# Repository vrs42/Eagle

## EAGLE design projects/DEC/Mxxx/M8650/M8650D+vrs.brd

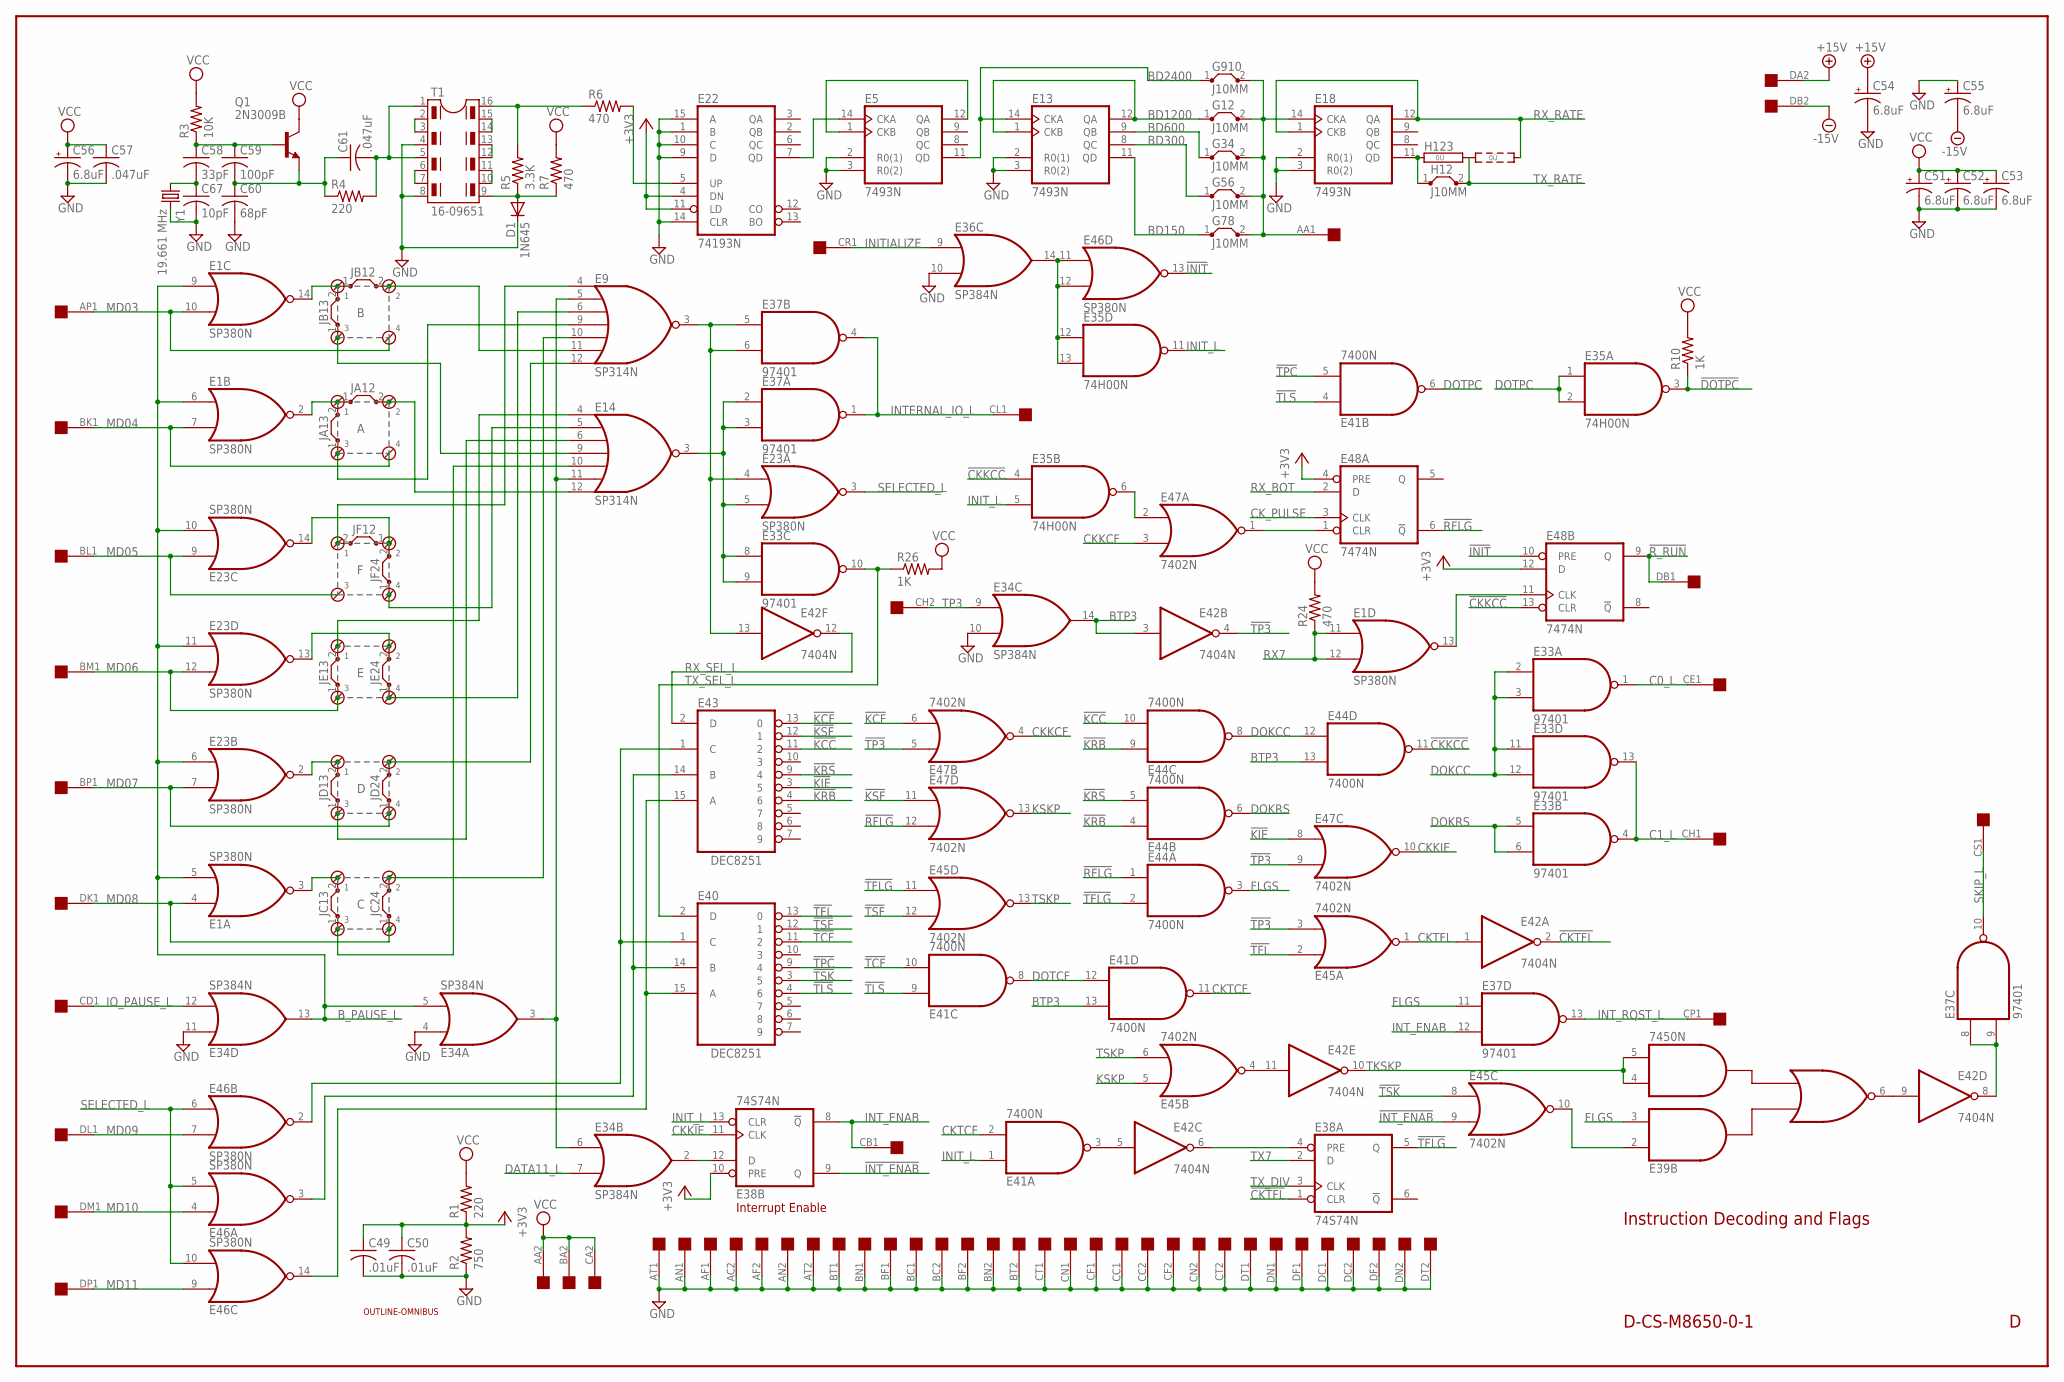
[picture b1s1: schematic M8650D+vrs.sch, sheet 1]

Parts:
A: JUMPER4
B: JUMPER4
C: JUMPER4
C49, C50: .01uF; C050-025X075
C51, C52, C53, C54, C55, C56: 6.8uF; E12-8
C57, C61: .047uF; C050-025X075
C58: 33pF; C050-025X075
C59: 100pF; C050-025X075
C60: 68pF; C050-025X075
C67: 10pF; C050-025X075
D: JUMPER4
D1: 1N645; DO35-10
E: JUMPER4
E1, E23, E46: SP380N; DIL14
E5, E13, E18: 7493N; DIL14
E9, E14: SP314N; DIL14
E22: 74193N; DIL16
E33, E37: 97401; DIL14
E34, E36: SP384N; DIL14
E35: 74H00N; DIL14
E38: 74S74N; DIL14
E39: 7450N; DIL14
E40, E43: DEC8251; DIL16
E41, E44: 7400N; DIL14
E42: 7404N; DIL14
E45, E47: 7402N; DIL14
E48: 7474N; DIL14
F: JUMPER4
G12, G34, G56, G78, G910: J10MM; 10
H12: J10MM; 10
H123: 0R2; 0R2/10
JA12, JA13: J10MM; 10
JB12, JB13: J10MM; 10
JC13, JC24: J10MM; 10
JD13, JD24: J10MM; 10
JE13, JE24: J10MM; 10
JF12, JF24: J10MM; 10
Q1: 2N3009B; TO5
R1, R4: 220; 0207/10
R2: 750; 0207/10
R3: 10K; 0207/10
R5: 3.3K; 0207/10
R6, R7, R24: 470; 0207/10
R10, R26: 1K; 0207/10
T1: 16-09651; DIL16
U$1: OUTLINE-OMNIBUS; OMNIBUS
U$2: QUAD; EDGE-CON8
Y1: 19.661 MHz; HC49TL-H

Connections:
!CKKCC: E35.4 (I0), E44.11 (O), E48.13 (CLR)
!CKTFL: E38.1 (CLR), E42.2 (O)
!DOTPC: E35.3 (O), R10.1; also elsewhere on the board
!INIT: E46.13 (O), E48.10 (PRE); also elsewhere on the board
!INT_ENAB: E38.9 (Q), E45.9 (I1)
!KCC: E43.11 (2), E44.10 (I1)
!KCF: E43.13 (0), E47.6 (I1)
!KIE: E43.3 (5), E47.8 (I0)
!KRB: E43.4 (6), E44.4 (I0), E44.9 (I0)
!KRS: E43.9 (4), E44.5 (I1)
!KSF: E43.12 (1), E47.11 (I0)
!RFLG: E44.1 (I0), E47.12 (I1), E48.6 (!Q)
!R_RUN: E48.9 (Q), U$2.DB1; also elsewhere on the board
!TCF: E40.11 (2), E41.10 (I1)
!TFL: E40.13 (0), E45.2 (I0)
!TFLG: E38.5 (Q), E44.2 (I1), E45.11 (I0)
!TLS: E40.4 (6), E41.4 (I0), E41.9 (I0)
!TP3: E42.4 (O), E45.3 (I1), E47.5 (I0), E47.9 (I1)
!TPC: E40.9 (4), E41.5 (I1)
!TSF: E40.12 (1), E45.12 (I1)
!TSK: E40.3 (5), E45.8 (I0)
+3V3: C49.1, C50.1, E22.4 (DN), E22.11 (LD), E38.10 (PRE), E48.4 (PRE), E48.12 (D), R1.1, R2.2; also elsewhere on the board
+15V: C54.+, U$2.DA2; also elsewhere on the board
-15V: C55.-, U$2.DB2; also elsewhere on the board
BD150: E13.11 (QD), G78.1
BD300: E13.8 (QC), G56.1
BD600: E13.9 (QB), G34.1
BD1200: E13.1 (CKB), E13.12 (QA), G12.1
BD2400: E5.11 (QD), E13.14 (CKA), G910.1
BTP3: E34.14 (O), E41.13 (I1), E42.3 (I), E44.13 (I1); also elsewhere on the board
B_PAUSE_L: E1.5 (I1), E1.6 (I0), E1.9 (I0), E23.6 (I0), E23.10 (I1), E23.11 (I0), E34.5 (I1), E34.13 (O)
C0_L: E33.1 (O), U$2.CE1
C1_L: E33.4 (O), E33.13 (O), U$2.CH1
CKKCF: E47.3 (I1), E47.4 (O)
CKKIE: E38.11 (CLK), E47.10 (O)
CKTCF: E41.2 (I1), E41.11 (O)
CKTFL: E42.1 (I), E45.1 (O)
CK_PULSE: E48.3 (CLK); also elsewhere on the board
DATA11_L: E34.7 (I1); also elsewhere on the board
DOKCC: E33.2 (I0), E33.3 (I1), E33.11 (I0), E33.12 (I1), E44.8 (O), E44.12 (I0)
DOKRS: E33.5 (I0), E33.6 (I1), E44.6 (O); also elsewhere on the board
DOTCF: E41.8 (O), E41.12 (I0)
DOTPC: E35.1 (I0), E35.2 (I1), E41.6 (O); also elsewhere on the board
FLGS: E37.11 (I0), E39.3 (I2), E44.3 (O)
GND: C49.2, C50.2, C51.-, C52.-, C53.-, C54.-, C55.+, C56.-, C57.2, C60.2, C67.2, D1.C, E1.1 (GND), E5.2 (R0(1)), E5.3 (R0(2)), E5.10 (GND), E9.1 (GND), E13.2 (R0(1)), E13.3 (R0(2)), E13.10 (GND), E14.1 (GND), E18.2 (R0(1)), E18.3 (R0(2)), E18.10 (GND), E22.1 (B), E22.8 (GND), E22.9 (D), E22.10 (C), E22.14 (CLR), E22.15 (A), E23.1 (GND), E33.7 (GND), E34.1 (GND), E34.4 (I0), E34.10 (I1), E34.11 (I0), E35.7 (GND), E36.1 (GND), E36.10 (I1), E37.7 (GND), E38.7 (GND), E39.7 (GND), E40.8 (GND), E41.7 (GND), E42.7 (GND), E43.8 (GND), E44.7 (GND), E45.7 (GND), E46.1 (GND), E47.7 (GND), E48.7 (GND), R2.1, T1.4, T1.8, U$2.AC2, U$2.AF1, U$2.AF2, U$2.AN1, U$2.AN2, U$2.AT1, U$2.AT2, U$2.BC1, U$2.BC2, U$2.BF1, U$2.BF2, U$2.BN1, U$2.BN2, U$2.BT1, U$2.BT2, U$2.CC1, U$2.CC2, U$2.CF1, U$2.CF2, U$2.CN1, U$2.CN2, U$2.CT1, U$2.CT2, U$2.DC1, U$2.DC2, U$2.DF1, U$2.DF2, U$2.DN1, U$2.DN2, U$2.DT1, U$2.DT2, Y1.2; also elsewhere on the board
INITIALIZE: E36.9 (I0), U$2.CR1
INIT_L: E35.5 (I1), E35.11 (O), E38.13 (CLR), E41.1 (I0); also elsewhere on the board
INTERNAL_IO_L: E37.1 (O), E37.4 (O), U$2.CL1
INT_ENAB: E37.12 (I1), E38.8 (!Q), U$2.CB1
INT_RQST_L: E37.13 (O), U$2.CP1
IO_PAUSE_L: E34.12 (I1), U$2.CD1
KSKP: E45.5 (I0), E47.13 (O)
MD03: B.4, E1.10 (I1), U$2.AP1
MD04: A.4, E1.7 (I1), U$2.BK1
MD05: E23.9 (I0), F.3, U$2.BL1
MD06: E.3, E23.12 (I1), JE13.1, U$2.BM1
MD07: D.4, E23.7 (I1), JD24.1, U$2.BP1
MD08: C.4, E1.4 (I0), JC24.1, U$2.DK1
MD09: E46.7 (I1), U$2.DL1
MD10: E46.4 (I0), U$2.DM1
MD11: E46.9 (I0), U$2.DP1
unnamed: E14.5 (I1), F.4, JF24.1
unnamed: E9.5 (I1), E14.11 (I5), E34.3 (O), E34.6 (I0)
unnamed: A.3, E9.9 (I3), JA13.1
unnamed: E9.3 (O), E23.4 (I0), E37.5 (I0), E37.6 (I1), E42.13 (I)
unnamed: E14.3 (O), E23.5 (I1), E33.8 (I0), E33.9 (I1), E37.2 (I0), E37.3 (I1)
unnamed: E34.2 (O), E38.12 (D)
unnamed: T1.6, T1.7
unnamed: E42.11 (I), E45.4 (O)
unnamed: T1.2, T1.3
unnamed: T1.14, T1.15
unnamed: T1.12, T1.13
unnamed: E35.12 (I0), E35.13 (I1), E36.14 (O), E46.11 (I0), E46.12 (I1)
unnamed: T1.10, T1.11
unnamed: E41.3 (O), E42.5 (I)
unnamed: E38.4 (PRE), E42.6 (O)
unnamed: E39.2 (I1), E45.10 (O)
unnamed: E39.6 (O), E42.9 (I)
unnamed: E40.14 (B), E43.14 (B), E46.3 (O)
unnamed: E37.8 (I0), E37.9 (I1), E42.8 (O)
unnamed: E40.1 (C), E43.1 (C), E46.2 (O)
unnamed: E40.15 (A), E43.15 (A), E46.14 (O)
unnamed: E1.13 (O), E48.11 (CLK)
unnamed: E47.1 (O), E48.1 (CLR)
unnamed: E35.6 (O), E47.2 (I0)
unnamed: B.3, E14.9 (I3), JB13.1
unnamed: B.1, E1.14 (O), JB12.1, JB13.2
unnamed: B.2, E9.11 (I5), JB12.2
unnamed: D.3, E14.6 (I2), JD13.1
unnamed: A.1, E1.2 (O), JA12.1, JA13.2
unnamed: C58.2, C67.1, Y1.1
unnamed: A.2, E14.12 (I6), JA12.2
unnamed: E.1, E14.4 (I0), JE13.2
unnamed: E.4, E9.6 (I2), JE24.1
unnamed: E.2, E23.13 (O), JE24.2
unnamed: D.2, E9.12 (I6), JD24.2
unnamed: D.1, E23.2 (O), JD13.2
unnamed: C.1, E1.3 (O), JC13.2
unnamed: C.3, E14.10 (I4), JC13.1
unnamed: C.2, E9.10 (I4), JC24.2
unnamed: C58.1, C59.1, Q1.2 (B), R3.1
unnamed: C59.2, C60.1, C61.1, Q1.1 (E), R4.1
unnamed: C61.2, R4.2, T1.1, T1.5
unnamed: R5.2, R6.1, T1.16
unnamed: D1.A, R5.1, R7.1, T1.9
unnamed: E22.5 (UP), R6.2
unnamed: E5.14 (CKA), E22.7 (QD)
unnamed: E5.1 (CKB), E5.12 (QA)
unnamed: E23.14 (O), F.2, JF12.1, JF24.2
unnamed: E18.11 (QD), H12.1, H123.1
unnamed: E9.4 (I0), F.1, JF12.2
RX7: E1.11 (I0), E1.12 (I1), R24.1; also elsewhere on the board
RX_BOT: E48.2 (D); also elsewhere on the board
RX_RATE: E18.1 (CKB), E18.12 (QA), H123.3; also elsewhere on the board
RX_SEL_L: E42.12 (O), E43.2 (D)
SELECTED_L: E23.3 (O), E46.5 (I1), E46.6 (I0), E46.10 (I1)
SKIP_L: E37.10 (O), U$2.CS1
TESTP4: E18.14 (CKA), G12.2, G34.2, G56.2, G78.2, G910.2, U$2.AA1
TKSKP: E39.4 (I3), E39.5 (I4), E42.10 (O)
TP3: E34.9 (I0), U$2.CH2
TSKP: E45.6 (I1), E45.13 (O)
TX7: E38.2 (D); also elsewhere on the board
TX_DIV: E38.3 (CLK); also elsewhere on the board
TX_RATE: H12.2, H123.2; also elsewhere on the board
TX_SEL_L: E33.10 (O), E40.2 (D), R26.1
VCC: C51.+, C52.+, C53.+, C56.+, C57.1, E1.8 (VCC), E5.5 (VCC), E9.8 (VCC), E13.5 (VCC), E14.8 (VCC), E18.5 (VCC), E22.16 (VCC), E23.8 (VCC), E33.14 (VCC), E34.8 (VCC), E35.14 (VCC), E36.8 (VCC), E37.14 (VCC), E38.14 (VCC), E39.14 (VCC), E40.16 (VCC), E41.14 (VCC), E42.14 (VCC), E43.16 (VCC), E44.14 (VCC), E45.14 (VCC), E46.8 (VCC), E47.14 (VCC), E48.14 (VCC), Q1.3 (C), R1.2, R3.2, R7.2, R10.2, R24.2, R26.2, U$2.AA2, U$2.BA2, U$2.CA2; also elsewhere on the board

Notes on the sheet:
Instruction Decoding and Flags
D-CS-M8650-0-1
Interrupt Enable

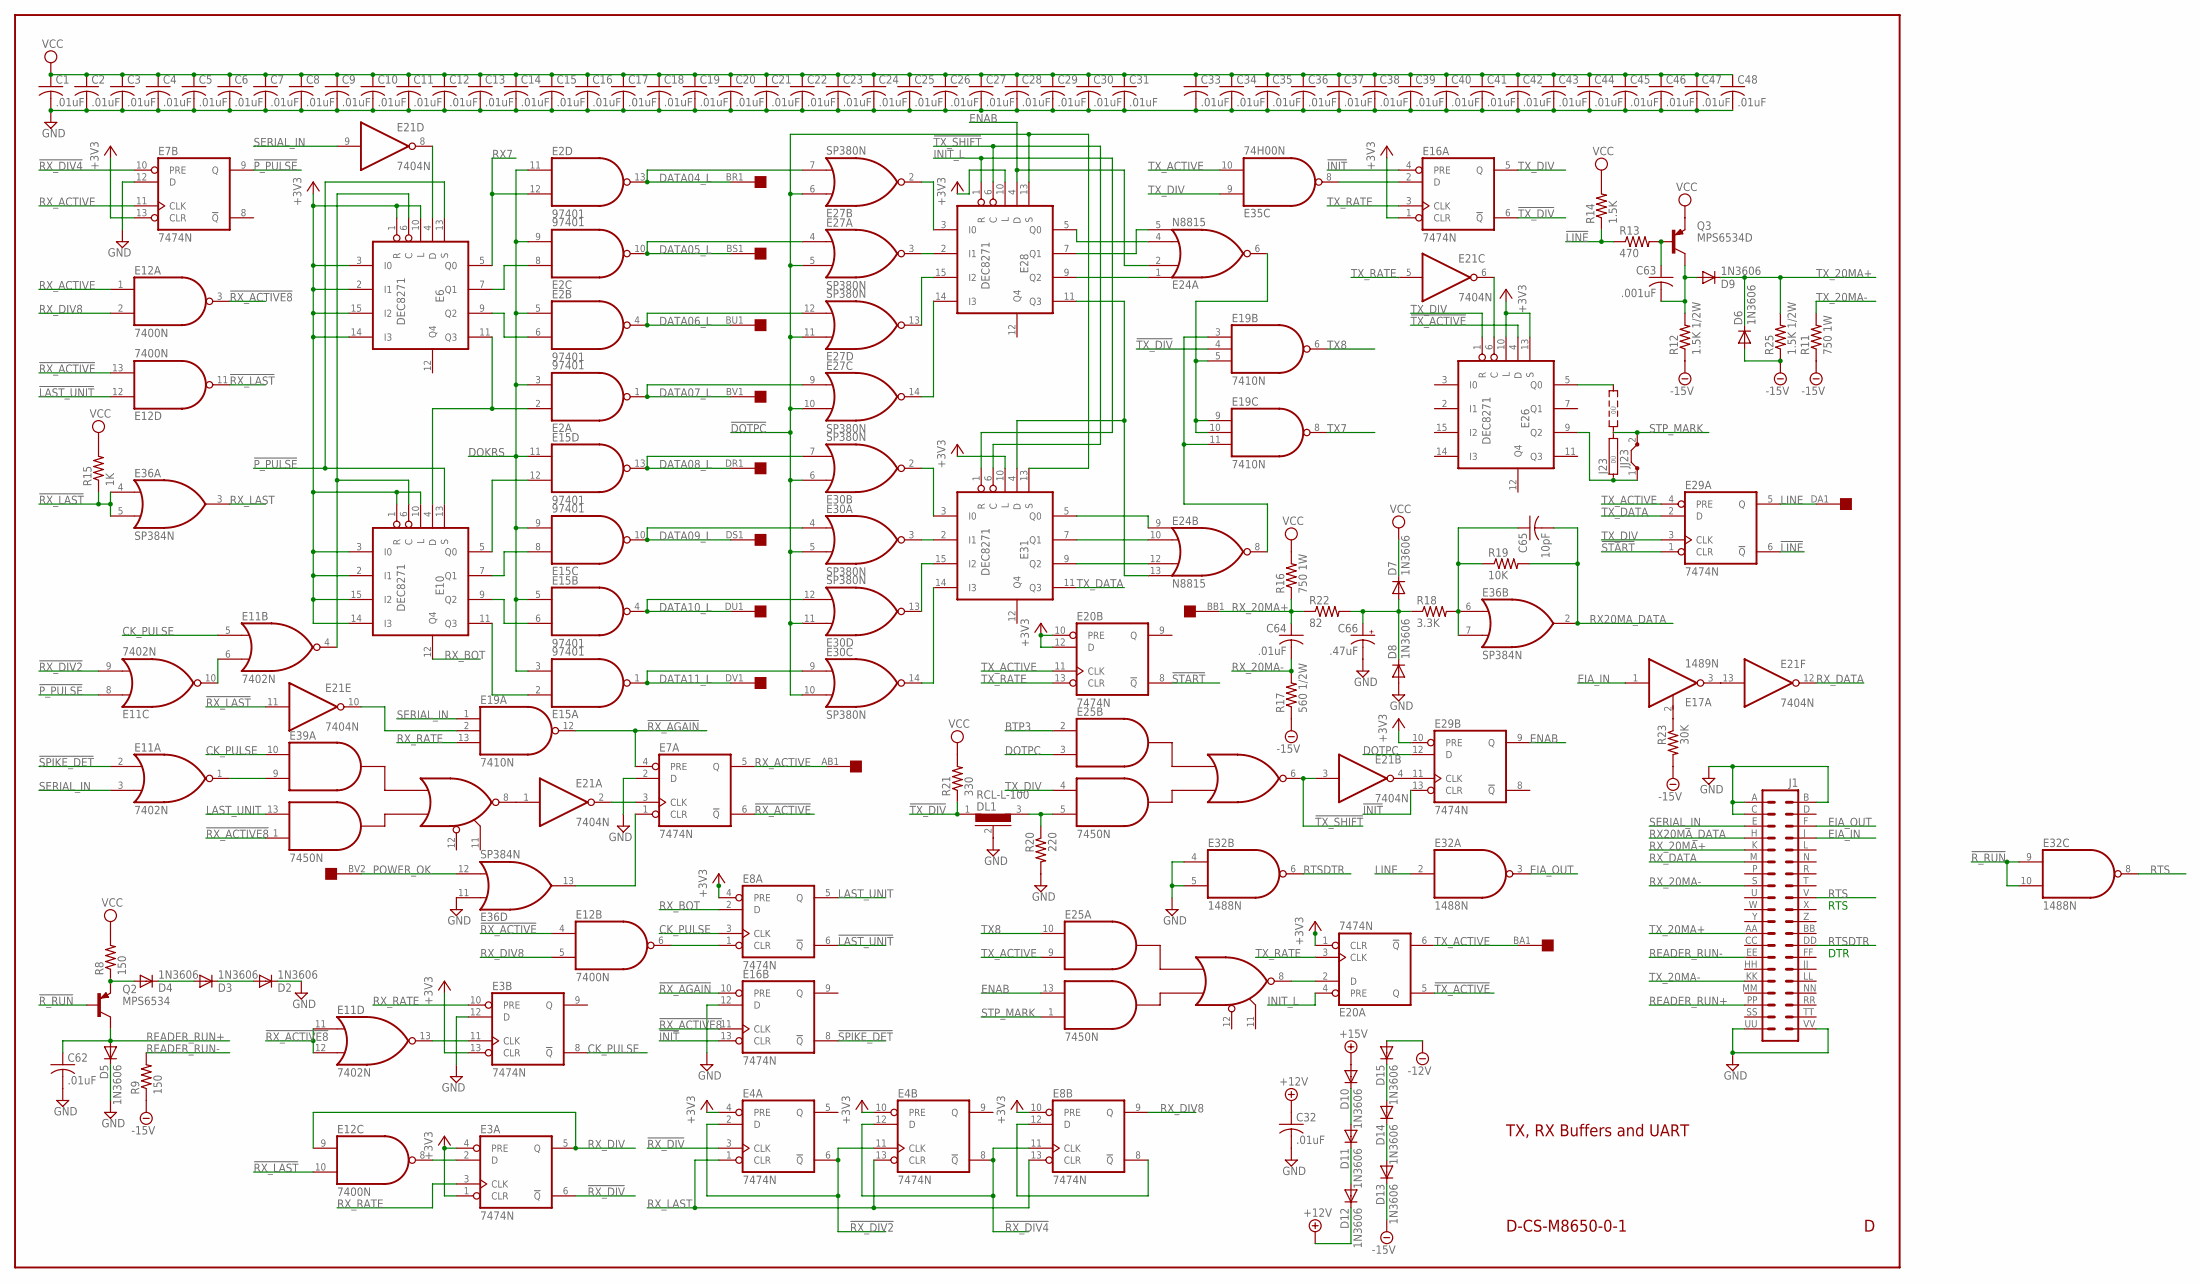
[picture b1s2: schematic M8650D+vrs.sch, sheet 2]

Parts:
C1, C2, C3, C4, C5, C6, C7, C8, C9, C10, C11, C12, C13, C14, C15, C16, C17, C18, C19, C20, C21, C22, C23, C24, C25, C26, C27, C28, C29, C30, C31, C32, C33, C34, C35, C36, C37, C38, C39, C40, C41, C42, C43, C44, C45, C46, C47, C48, C62, C64: .01uF; C050-025X075
C63: .001uF; C050-025X075
C65: 10pF; C050-025X075
C66: .47uF; E15-5
D2, D3, D4, D5, D6, D7, D8, D9, D10, D11, D12, D13, D14, D15: 1N3606; DO35-10
DL1: RCL-L-100; RCL-L-00-05
E2, E15: 97401; DIL14
E3, E4, E7, E8, E16, E20, E29: 7474N; DIL14
E6, E10, E26, E28, E31: DEC8271; DIL16
E11: 7402N; DIL14
E12: 7400N; DIL14
E17: 1489N; DIL14
E19: 7410N; DIL14
E21: 7404N; DIL14
E24: N8815; DIL14
E25, E39: 7450N; DIL14
E27, E30: SP380N; DIL14
E32: 1488N; DIL14
E35: 74H00N; DIL14
E36: SP384N; DIL14
J1: DEC40PINH
J23: 0R2; 0R2/10
JJ23: J10MM; 10
Q2: MPS6534; TO5
Q3: MPS6534D; TO5
R8, R9: 150; 0207/10
R11, R16: 750 1W; 0617/17
R12, R25: 1.5K 1/2W; 0411/15
R13: 470; 0207/10
R14: 1.5K; 0207/10
R15: 1K; 0207/10
R17: 560 1/2W; 0411/15
R18: 3.3K; 0207/10
R19: 10K; 0207/10
R20: 220; 0207/10
R21: 330; 0207/10
R22: 82; 0207/10
R23: 30K; 0207/10
U$2: QUAD; EDGE-CON8

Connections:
!DOTPC: E27.5 (I1), E27.6 (I0), E27.10 (I1), E27.11 (I0), E28.13 (S), E30.5 (I1), E30.6 (I0), E30.10 (I1), E30.11 (I0), E31.13 (S); also elsewhere on the board
!INIT: E16.4 (PRE), E16.13 (CLR), E29.13 (CLR); also elsewhere on the board
!LAST_UNIT: E8.6 (!Q), E12.12 (I0)
!LINE: E29.6 (!Q), R13.1, R14.1
!P_PULSE: E6.13 (S), E7.9 (Q), E10.13 (S), E11.8 (I0)
!RX_ACTIVE: E7.6 (!Q), E12.4 (I0), E12.13 (I1)
!RX_ACTIVE8: E11.11 (I0), E11.12 (I1), E12.3 (O), E16.11 (CLK), E39.1 (I4)
!RX_AGAIN: E7.4 (PRE), E16.10 (PRE), E19.12 (O)
!RX_DIV: E3.6 (!Q), E4.3 (CLK)
!RX_DIV2: E4.2 (D), E4.6 (!Q), E4.11 (CLK), E11.9 (I1)
!RX_DIV4: E4.8 (!Q), E4.12 (D), E7.10 (PRE), E8.11 (CLK)
!RX_LAST: E12.10 (I1), E12.11 (O), E21.11 (I), E36.4 (I0), E36.5 (I1), R15.1
!R_RUN: E32.9 (I0), E32.10 (I1), Q2.2 (B); also elsewhere on the board
!SPIKE_DET: E11.2 (I0), E16.8 (!Q)
!START: E20.8 (!Q), E29.1 (CLR)
!TX_ACTIVE: E20.5 (Q), E26.4 (D)
!TX_DIV: DL1.1, E16.6 (!Q), E19.4 (I1), R21.1
!TX_SHIFT: E21.3 (I), E25.6 (O), E28.6 (C), E31.6 (C)
+3V3: E3.1 (CLR), E3.4 (PRE), E3.13 (CLR), E4.4 (PRE), E4.10 (PRE), E6.1 (R), E6.2 (I1), E6.3 (I0), E6.10 (L), E6.14 (I3), E6.15 (I2), E7.13 (CLR), E8.4 (PRE), E8.10 (PRE), E10.1 (R), E10.2 (I1), E10.3 (I0), E10.10 (L), E10.14 (I3), E10.15 (I2), E16.1 (CLR), E20.1 (CLR), E20.10 (PRE), E20.12 (D), E26.10 (L), E26.13 (S), E28.10 (L), E29.10 (PRE), E31.10 (L); also elsewhere on the board
+12V: C32.1, D12.C, E32.14 (+12V)
+15V: D10.A; also elsewhere on the board
-12V: D15.A, E32.1 (-12V)
-15V: D6.A, D13.C, R9.1, R11.1, R12.1, R17.1, R23.2, R25.1; also elsewhere on the board
BTP3: E25.2 (I1); also elsewhere on the board
CK_PULSE: E3.8 (!Q), E8.3 (CLK), E11.5 (I0), E39.10 (I1); also elsewhere on the board
DATA04_L: E2.13 (O), E27.7 (I1), U$2.BR1
DATA05_L: E2.10 (O), E27.4 (I0), U$2.BS1
DATA06_L: E2.4 (O), E27.12 (I1), U$2.BU1
DATA07_L: E2.1 (O), E27.9 (I0), U$2.BV1
DATA08_L: E15.13 (O), E30.7 (I1), U$2.DR1
DATA09_L: E15.10 (O), E30.4 (I0), U$2.DS1
DATA10_L: E15.4 (O), E30.12 (I1), U$2.DU1
DATA11_L: E15.1 (O), E30.9 (I0), U$2.DV1; also elsewhere on the board
DOKRS: E2.3 (I1), E2.5 (I0), E2.9 (I1), E2.11 (I0), E15.3 (I1), E15.5 (I0), E15.9 (I1), E15.11 (I0); also elsewhere on the board
DOTPC: E25.3 (I2), E29.12 (D); also elsewhere on the board
EIA_IN: E17.1 (I), J1.J (8)
EIA_OUT: E32.3 (O), J1.F (6)
ENAB: E24.2 (I1), E25.13 (I3), E28.4 (D), E29.9 (Q)
GND: C1.2, C2.2, C3.2, C4.2, C5.2, C6.2, C7.2, C8.2, C9.2, C10.2, C11.2, C12.2, C13.2, C14.2, C15.2, C16.2, C17.2, C18.2, C19.2, C20.2, C21.2, C22.2, C23.2, C24.2, C25.2, C26.2, C27.2, C28.2, C29.2, C30.2, C31.2, C32.2, C33.2, C34.2, C35.2, C36.2, C37.2, C38.2, C39.2, C40.2, C41.2, C42.2, C43.2, C44.2, C45.2, C46.2, C47.2, C48.2, C62.2, C66.-, D2.C, D5.C, D8.A, DL1.2, E2.7 (GND), E3.7 (GND), E3.12 (D), E4.7 (GND), E6.8 (GND), E7.2 (D), E7.7 (GND), E7.12 (D), E8.7 (GND), E10.8 (GND), E11.7 (GND), E12.7 (GND), E15.7 (GND), E16.7 (GND), E16.12 (D), E17.7 (GND), E19.7 (GND), E20.7 (GND), E21.7 (GND), E24.7 (GND), E25.7 (GND), E26.8 (GND), E27.1 (GND), E28.8 (GND), E29.7 (GND), E30.1 (GND), E31.8 (GND), E32.4 (I0), E32.5 (I1), E32.7 (GND), E35.7 (GND), E36.1 (GND), E36.11 (I0), E39.7 (GND), J1.A (1), J1.B (2), J1.C (3), J1.UU (39), J1.VV (40), R20.2; also elsewhere on the board
INIT_L: E20.4 (PRE), E28.1 (R), E31.1 (R); also elsewhere on the board
LAST_UNIT: E8.5 (Q), E39.13 (I3)
LINE: E29.5 (Q), E32.2 (I), U$2.DA1
unnamed: D2.A, D3.C
unnamed: E2.8 (I0), E6.7 (Q1)
unnamed: E2.2 (I0), E6.11 (Q3), E10.4 (D)
unnamed: E2.6 (I1), E6.9 (Q2)
unnamed: E10.5 (Q0), E15.12 (I1)
unnamed: E10.7 (Q1), E15.8 (I0)
unnamed: E10.9 (Q2), E15.6 (I1)
unnamed: E10.11 (Q3), E15.2 (I0)
unnamed: E6.6 (C), E10.6 (C), E11.4 (O)
unnamed: E11.6 (I1), E11.10 (O)
unnamed: E6.4 (D), E21.8 (O)
unnamed: E27.2 (O), E28.3 (I0)
unnamed: E27.3 (O), E28.2 (I1)
unnamed: E27.13 (O), E28.15 (I2)
unnamed: E27.14 (O), E28.14 (I3)
unnamed: E30.2 (O), E31.3 (I0)
unnamed: E30.3 (O), E31.2 (I1)
unnamed: E30.13 (O), E31.15 (I2)
unnamed: E30.14 (O), E31.14 (I3)
unnamed: E24.1 (I0), E28.9 (Q2)
unnamed: E24.4 (I2), E28.5 (Q0)
unnamed: E24.13 (I3), E28.11 (Q3), E31.4 (D)
unnamed: E24.5 (I3), E28.7 (Q1)
unnamed: E24.9 (I0), E31.5 (Q0)
unnamed: E24.10 (I1), E31.7 (Q1)
unnamed: E24.12 (I2), E31.9 (Q2)
unnamed: E7.3 (CLK), E21.2 (O)
unnamed: E19.3 (I0), E19.11 (I2), E24.8 (O)
unnamed: E19.5 (I2), E19.9 (I0), E19.10 (I1), E24.6 (O)
unnamed: E21.1 (I), E39.8 (O)
unnamed: E7.1 (CLR), E36.13 (O)
unnamed: C63.2, D9.A, Q3.3 (C), R12.2
unnamed: E3.2 (D), E12.8 (O)
unnamed: E17.2 (RC), R23.1
unnamed: E19.2 (I1), E21.10 (O)
unnamed: D13.A, D14.C
unnamed: E11.1 (O), E39.9 (I2)
unnamed: E3.11 (CLK), E11.13 (O)
unnamed: E17.3 (O), E21.13 (I)
unnamed: E8.8 (!Q), E8.12 (D)
unnamed: E8.1 (CLR), E12.6 (O)
unnamed: E16.2 (D), E35.8 (O)
unnamed: E21.4 (O), E29.11 (CLK)
unnamed: DL1.3, E25.5 (I4), R20.1
unnamed: E20.2 (D), E25.8 (O)
unnamed: E26.9 (Q2), J23.1, JJ23.1
unnamed: D4.A, Q2.1 (E), R8.1
unnamed: D3.A, D4.C
unnamed: D14.A, D15.C
unnamed: C66.+, D7.A, D8.C, R18.1, R22.2
unnamed: D10.C, D11.A
unnamed: D11.C, D12.A
unnamed: C65.1, E36.6 (I0), E36.7 (I1), R18.2, R19.1
unnamed: C63.1, Q3.2 (B), R13.2
unnamed: E21.6 (O), E26.6 (C)
unnamed: E26.5 (Q0), J23.3
POWER_OK: E36.12 (I1), U$2.BV2
READER_RUN+: C62.1, D5.A, J1.PP (35), Q2.3 (C)
READER_RUN-: J1.EE (27), R9.2
RTS: E32.8 (O), J1.V (18)
RTSDTR: E32.6 (O), J1.DD (26)
RX7: E2.12 (I1), E6.5 (Q0); also elsewhere on the board
RX20MA_DATA: C65.2, E36.2 (O), J1.H (7), R19.2
RX_20MA+: C64.1, J1.K (9), R16.1, R22.1, U$2.BB1
RX_20MA-: C64.2, J1.S (15), R17.2
RX_ACTIVE: E7.5 (Q), E7.11 (CLK), E12.1 (I0), U$2.AB1
RX_BOT: E8.2 (D), E10.12 (Q4); also elsewhere on the board
RX_DATA: E21.12 (O), J1.M (11)
RX_DIV: E3.5 (Q), E12.9 (I0)
RX_DIV8: E8.9 (Q), E12.2 (I1), E12.5 (I1)
RX_LAST: E4.1 (CLR), E4.13 (CLR), E8.13 (CLR), E36.3 (O)
RX_RATE: E3.3 (CLK), E3.10 (PRE), E19.13 (I2); also elsewhere on the board
SERIAL_IN: E11.3 (I1), E19.1 (I0), E21.9 (I), J1.E (5)
STP_MARK: E25.1 (I4), J23.2, JJ23.2
TX7: E19.8 (O); also elsewhere on the board
TX8: E19.6 (O), E25.10 (I1)
TX_20MA+: D6.C, D9.C, J1.AA (23), R25.2
TX_20MA-: J1.KK (31), R11.2
TX_ACTIVE: E20.6 (!Q), E20.11 (CLK), E25.9 (I2), E29.4 (PRE), E35.10 (I1), U$2.BA1
TX_DATA: E29.2 (D), E31.11 (Q3)
TX_DIV: E16.5 (Q), E25.4 (I3), E26.1 (R), E29.3 (CLK), E35.9 (I0); also elsewhere on the board
TX_RATE: E16.3 (CLK), E20.3 (CLK), E20.13 (CLR), E21.5 (I); also elsewhere on the board
VCC: C1.1, C2.1, C3.1, C4.1, C5.1, C6.1, C7.1, C8.1, C9.1, C10.1, C11.1, C12.1, C13.1, C14.1, C15.1, C16.1, C17.1, C18.1, C19.1, C20.1, C21.1, C22.1, C23.1, C24.1, C25.1, C26.1, C27.1, C28.1, C29.1, C30.1, C31.1, C33.1, C34.1, C35.1, C36.1, C37.1, C38.1, C39.1, C40.1, C41.1, C42.1, C43.1, C44.1, C45.1, C46.1, C47.1, C48.1, D7.C, E2.14 (VCC), E3.14 (VCC), E4.14 (VCC), E6.16 (VCC), E7.14 (VCC), E8.14 (VCC), E10.16 (VCC), E11.14 (VCC), E12.14 (VCC), E15.14 (VCC), E16.14 (VCC), E17.14 (VCC), E19.14 (VCC), E20.14 (VCC), E21.14 (VCC), E24.14 (VCC), E25.14 (VCC), E26.16 (VCC), E27.8 (VCC), E28.16 (VCC), E29.14 (VCC), E30.8 (VCC), E31.16 (VCC), E35.14 (VCC), E36.8 (VCC), E39.14 (VCC), Q3.1 (E), R8.2, R14.2, R15.2, R16.2, R21.2; also elsewhere on the board

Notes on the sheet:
D-CS-M8650-0-1
TX, RX Buffers and UART
RTS
DTR

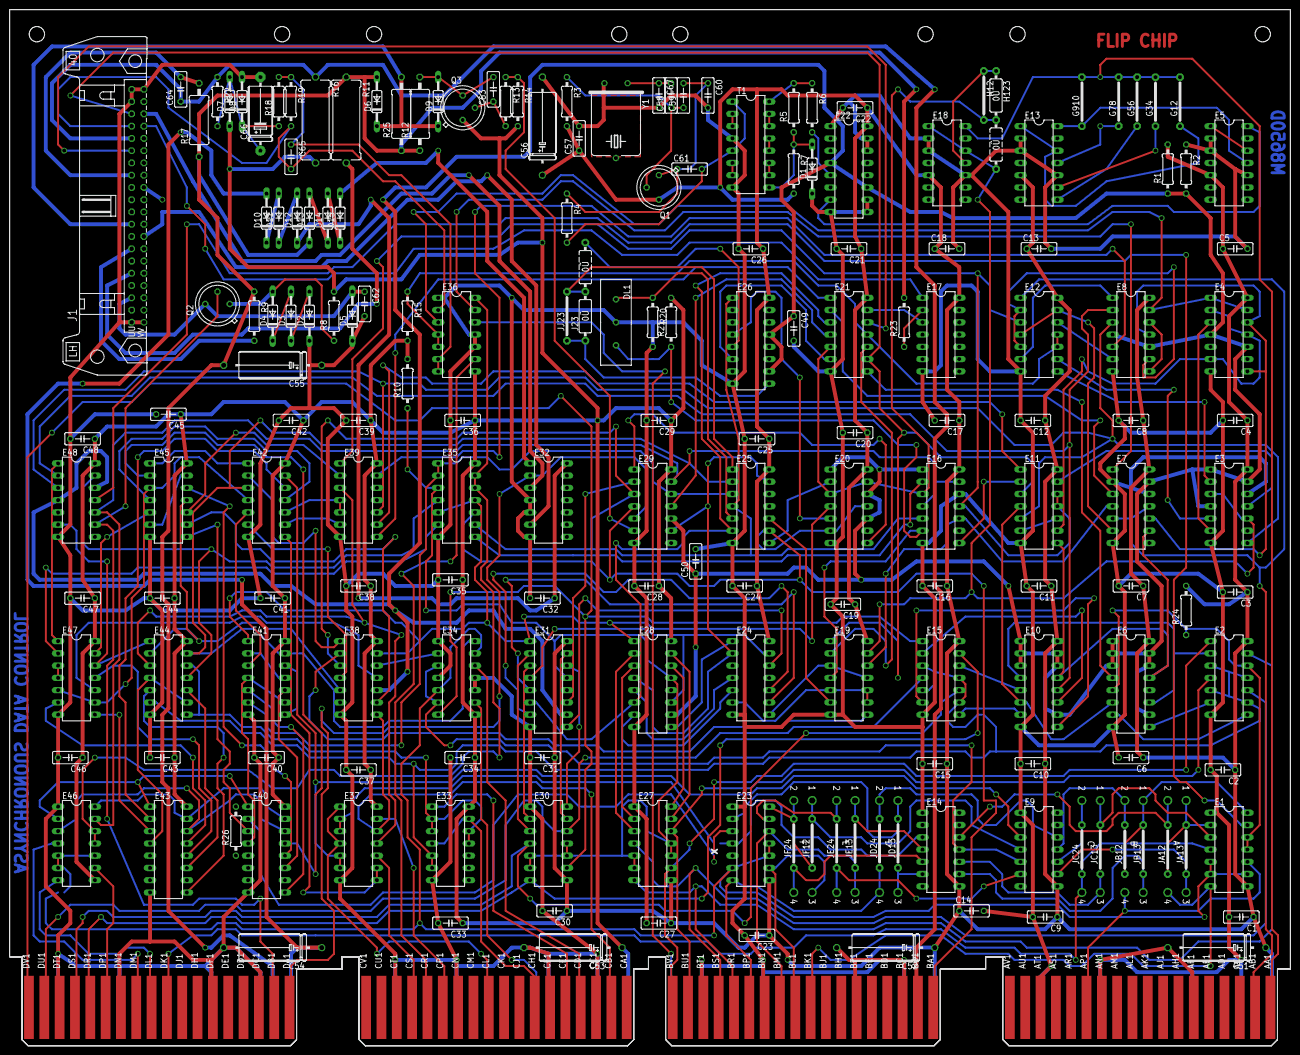
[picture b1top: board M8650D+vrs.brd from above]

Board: 4 copper layers, 265.3 x 214.6 mm, 193 parts (0 on the bottom side), 231 nets.

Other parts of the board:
U$3: FLIPCHIP
